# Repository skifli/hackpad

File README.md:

# hackpad

- [hackpad](#hackpad)
  - [Project Structure](#project-structure)
  - [Journal](#journal)
  - [PCB](#pcb)
    - [Schematic](#schematic)
    - [PCB Design](#pcb-design)
    - [PCB Render](#pcb-render)
  - [CAD](#cad)
  - [BOM](#bom)
  - [Software](#software)

| Cover                            | Exploded View                                    |
| -------------------------------- | ------------------------------------------------ |
|  |  |

> [!IMPORTANT]\
> Since submission, the BOM price has decreased to $119.89 from above $150 (check [#bom](#bom) for more information).

A fully wireless macropad with 14 Choc v1 Ambient Nocturnal switches, 2 rotary encoders (with a push-button each), and a small screen! The case is in two sections - a top and bottom, and joins together via 8 magnets, half in each side of the case (you can see the magnet holes in the various views).

I made this project because when programming / doing CAD design there are so many different shortcuts I use to make sketches, change orbit types, etc, and these require a lot of clicks. These all could be streamlined a lot more with the use of a macropad - which is why I made this one. I decided to also add a screen so I could easily see which profile I'm on and switch (likely by rotating a rotary encoder while it is held down), and the two rotary encoders to easily control multiple audio streams (mainly YouTube vs. Spotify).

## Project Structure

> [!IMPORTANT]\
> Only includes files / folders relevant to admin that would benefit from explanation.

```
└── 📁hackpad
    └── 📁design
        └── 📁cad
            ├── case_bottom.step
            ├── case_top.step
        └── 📁pcb
            ├── ... # Contains the KiCad directory for the PCB
        └── 📁plate
            ├── ... # Contains the KiCad directory for the plate, which is made from an exported DXF from the Fusion 360 Sketch (plate.dxf)
    ├── JOURNAL.md # The journal of the design process
    └── README.md # This file
```

> [!WARNING]\
> The KiCad plate PCB gives [malformed outline warnings](JOURNAL.md#20072025) and doesn't show correctly in 3D view - no idea why, but when exported with the Fabrication Toolkit and imported into JLCPCB it's totally fine 🗿 (if it works, it works™). 

## Journal

The [journal](JOURNAL.md) contains each day's work, logged, with the aid of images. Total time is at the top and each day has its time logged. There is also a Table of Contents for easy navigation :).

> [!NOTE]\
> Total time spent: **60h**

## PCB

### Schematic

### PCB Design

### PCB Render

## CAD

| Case Top Side View (from the bottom)                 | Case Bottom Side View (from the top)                       |
| ---------------------------------------------------- | ---------------------------------------------------------- |
|  |  |

| Case Plate                                     | Case USB Port                              |
| ---------------------------------------------- | ------------------------------------------ |
|  |  |

## BOM

> [!TIP]\
> The BOM is split into the different companies from which the components would be bought, with an empty line delimiting them. As well as this, at the end of each section, the total price for that provider, along with the shipping, is provided in the **Price** column. There is also the total price in the aforementioned column on the last row.

> [!NOTE]\
> I found the promo code **KBDNEWS** for Mechboards (a UK-based merchant) 5% off so I included that in the BOM as well to explain the decrease in total price.

<details closed>
<summary>BOM in table format</summary>

| Component                               | Description                     | Notes                                            | Qty | Price      | Shipping   | Provider   | Link                                                                                                               |
| --------------------------------------- | ------------------------------- | ------------------------------------------------ | --- | ---------- | ---------- | ---------- | ------------------------------------------------------------------------------------------------------------------ |
| Kailh Choc Hotswap Sockets              | V1 (Pack of 10)                 |                                                  | 2   | £6.00      | £1.81      | Mechboards | [Link](https://mechboards.co.uk/products/kailh-choc-hotswap-sockets?variant=40427263754445)                        |
| DDC Choc (v1) PBT Blank Keycaps - White | White Keycaps / 1u (Pack of 10) |                                                  | 1   | £4.50      | –          | Mechboards | [Link](https://mechboards.co.uk/products/ddc-choc-pbt-blank-keycaps?variant=47587896426701)                        |
| DDC Choc (v1) PBT Blank Keycaps - Black | Black Keycaps / 1u (Pack of 10) |                                                  | 1   | £4.50      | –          | Mechboards | [Link](https://mechboards.co.uk/products/ddc-choc-pbt-blank-keycaps?variant=47405364576461)                        |
| lowprokb Choc (V1) Ambients Nocturnal   | (Pack of 10)                    |                                                  | 2   | £19.00     | –          | Mechboards | [Link](https://mechboards.co.uk/products/lowprokb-ambients-silent-linear-nocturnal-choc-v1?variant=47588169908429) |
| KBDNEWS Promo Code                      |                                 |                                                  | –   | –£0.94     | –          | –          | –                                                                                                                  |
| **Total (Mechboards)**                  |                                 |                                                  |     | **£34.11** | *Included* |            |                                                                                                                    |
| nice!nano v2                            |                                 | Compatible board                                 | 1   | £2.99      | £2.99      | AliExpress | [Link](https://www.aliexpress.com/item/1005006035267231.html)                                                      |
| nice!view                               |                                 | Compatible screen (without headers)              | 1   | £12.69     | –          | AliExpress | [Link](https://www.aliexpress.com/item/1005008115497843.html)                                                      |
| Header Pins                             | 1x5 Pins (50 PCS)               | Headers for the above screen                     | 1   | £1.15      | –          | AliExpress | [Link](https://www.aliexpress.com/item/4000988113226.html)                                                         |
| Tiny Disc Magnet                        | 4x3mm (100 PCS)                 | To join the top and bottom of the case           | 1   | £4.86      | £2.96      | AliExpress | [Link](https://www.aliexpress.com/item/1005009177139622.html)                                                      |
| SMT SOD-123 Diodes                      | 100 PCS                         | For the switches                                 | 1   | £1.11      | –          | AliExpress | [Link](https://www.aliexpress.com/item/4000685043735.html)                                                         |
| Heat Shrink Tubes                       |                                 | For wiring between switch, battery, nice!nano v2 | 1   | £1.35      | –          | AliExpress | [Link](https://www.aliexpress.com/item/1005008146302901.html)                                                      |
| JST PH Plug Connector with Wire (M)     | MALE 2P 100mm (5 PCS)           | For battery wiring                               | 1   | £0.34      | £1.94      | AliExpress | [Link](https://www.aliexpress.com/item/1005008864177105.html)                                                      |
| JST PH Plug Connector with Wire (F)     | FEMALE 2P 100mm (5 PCS)         | For battery wiring                               | 1   | £0.49      | £1.94      | AliExpress | [Link](https://www.aliexpress.com/item/1005008864177105.html)                                                      |
| Bumper Feet                             | 5mm x 2mm (100 PCS)             | For bottom of the case and PCB                   | 1   | £1.59      | –          | AliExpress | [Link](https://www.aliexpress.com/item/1005004068119765.html)                                                      |
| Toggle Switch                           | K031b004-G3                     | To power on/off the system                       | 1   | £1.94      | –          | AliExpress | [Link](https://www.aliexpress.com/item/1005009306874094.html)                                                      |
| 3.7V 150mAh                             | 1 battery                       | To power the system                              | 1   | £4.74      | N/A        | AliExpress | [Link](https://www.aliexpress.com/item/1005004084377638.html)                                                      |
| Rotary Encoder w/ Push Button           | 5 PCS                           |                                                  | 1   | £1.08      | –          | AliExpress | [Link](https://www.aliexpress.com/item/1005005983134515.html)                                                      |
| **Total (AliExpress)**                  |                                 |                                                  |     | **£42.35** | *Included* |            |                                                                                                                    |
| Plate & PCB                             |                                 |                                                  |     | £5.94      | £6.11      | JLCPCB     | N/A                                                                                                                |
| **Total (JLCPCB)**                      |                                 |                                                  |     | **£12.05** | *Included* |            |                                                                                                                    |
| **TOTAL**                               |                                 |                                                  |     | **£88.51** | *Included* |            |                                                                                                                    |  |

</details>

> [!IMPORTANT]\
> Please disregard a lot of what is in the below text. After someone in the Slack (@Toby), introduced me to the world of AliExpress, I completely redid the BOM. It is now $119.89 (yes that is USD lol), so way under the limit. Thanks a lot dude :).

The BOM can be found in [`/bom.csv`](bom.csv). Since this is my first ever hardware project, I decided to go for some products that were easier to find footprints / symbols in KiCad for. With hindsight, spending the amount of money I now have to on a nice! nano v2 or nice!view (which I landed on because I chose the nice! nano v2) isn't really necessary. So, in future projects I'll choose other, cheaper components - but for this one I've already designed the PCB etc, and was very new to this whole world of design, and so decided to go with components that I was more confident with.

The Seeed Studio XIAO RP2040 didn't have enough GPIO anyway since I needed a 4x4 key matrix (so 8 pins), 4 other GPIO for the 2 rotary encoders, and the screen pins. Now, unfortunately this does mean the price is way over $150. This is in part because I also forgot Hackclub operates in USD and so was sure I would be in price range until 2 days ago, at which point I had a heart attack 😭. I'll try to cover the rest myself... not really sure how that'll go because I need to buy solder and other stuff since this is my first hardware project (which is already a lot of money), but we'll see... I'm not sure if Hackclub has a thing with JLCPCB for cheaper PCBs but if so that would reduce the total cost, although it might still be just over $150.

## Software

Will be _mostly_ added once the physical components are received and assembled, as I don't want to start writing code and then find out it doesn't work because I accidentally used libraries for different components, or something similar to that.

I have added some stuff in the [`/software`](software) directory though.

---
<sub>Thanks to [Hackclub](https://hackclub.com) for such an amazing opportunity - this project was made by [@skifli](https://github.com/skifli) with 🩷, under the [MIT License](LICENSE).</sub>

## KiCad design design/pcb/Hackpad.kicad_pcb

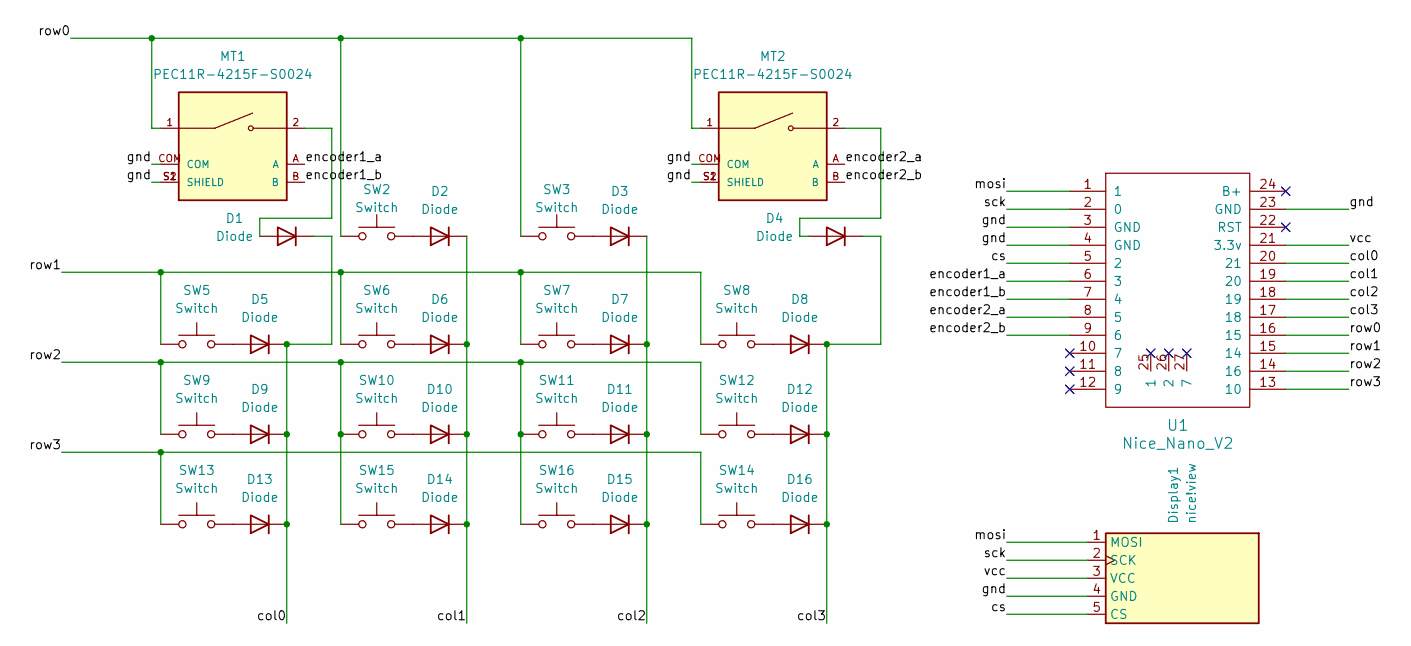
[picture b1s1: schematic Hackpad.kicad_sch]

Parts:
D1, D2, D3, D4, D5, D6, D7, D8, D9, D10, D11, D12, D13, D14, D15, D16: Diode; D_SOD-123; PARTREV 5
Display1: nice!view; nice_view
MT1, MT2: PEC11R-4215F-S0024; XDCR_PEC11R-4215F-S0024; PARTREV Rev. 09/19
SW2, SW3, SW5, SW6, SW7, SW8, SW9, SW10, SW11, SW12, SW13, SW14, SW15, SW16: Switch; Hotswap_Choc_V1_1.00u
U1: Nice_Nano_V2

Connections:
/col0: D1.1 (K), D5.1 (K), D9.1 (K), D13.1 (K), U1.20 (21)
/col1: D2.1 (K), D6.1 (K), D10.1 (K), D14.1 (K), U1.19 (20)
/col2: D3.1 (K), D7.1 (K), D11.1 (K), D15.1 (K), U1.18 (19)
/col3: D4.1 (K), D8.1 (K), D12.1 (K), D16.1 (K), U1.17 (18)
/cs: Display1.5 (CS), U1.5 (2)
/encoder1_a: MT1.A, U1.6 (3)
/encoder1_b: MT1.B, U1.7 (4)
/encoder2_a: MT2.A, U1.8 (5)
/encoder2_b: MT2.B, U1.9 (6)
/gnd: Display1.4 (GND), MT1.COM, MT1.S1 (SHIELD), MT1.S2 (SHIELD), MT2.COM, MT2.S1 (SHIELD), MT2.S2 (SHIELD), U1.3 (GND), U1.4 (GND), U1.23 (GND)
/mosi: Display1.1 (MOSI), U1.1
/row0: MT1.1, MT2.1, SW2.1, SW3.1, U1.16 (15)
/row1: SW5.1, SW6.1, SW7.1, SW8.1, U1.15 (14)
/row2: SW9.1, SW10.1, SW11.1, SW12.1, SW15.1, SW16.1, U1.14 (16)
/row3: SW13.1, SW14.1, U1.13 (10)
/sck: Display1.2 (SCK), U1.2 (0)
/vcc: Display1.3 (VCC), U1.21 (3.3v)
unnamed: D1.2 (A), MT1.2
unnamed: D2.2 (A), SW2.2
unnamed: D3.2 (A), SW3.2
unnamed: D4.2 (A), MT2.2
unnamed: D5.2 (A), SW5.2
unnamed: D6.2 (A), SW6.2
unnamed: D7.2 (A), SW7.2
unnamed: D8.2 (A), SW8.2
unnamed: D9.2 (A), SW9.2
unnamed: D10.2 (A), SW10.2
unnamed: D11.2 (A), SW11.2
unnamed: D12.2 (A), SW12.2
unnamed: D13.2 (A), SW13.2
unnamed: D14.2 (A), SW15.2
unnamed: D15.2 (A), SW16.2
unnamed: D16.2 (A), SW14.2

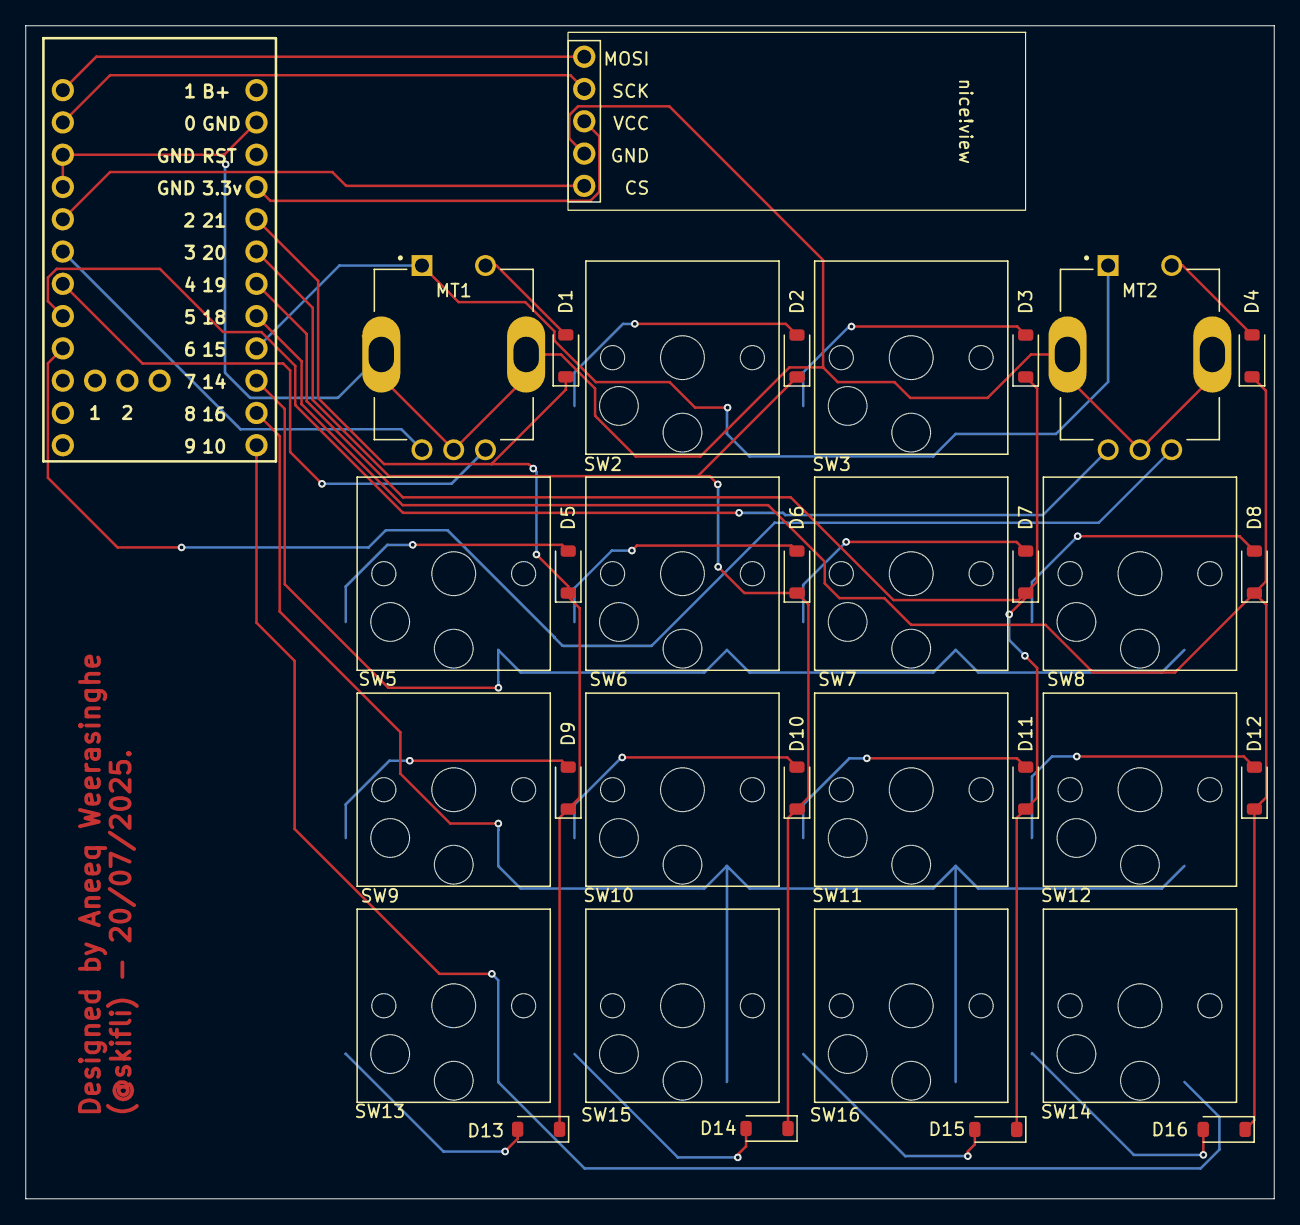
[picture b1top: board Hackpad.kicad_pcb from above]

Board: 2 copper layers, 98.2 x 92.3 mm, 34 parts (0 on the bottom side), 33 nets.

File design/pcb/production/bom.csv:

Designator,Footprint,Quantity,Value,LCSC Part #
"D1, D10, D11, D12, D13, D14, D15, D16, D2, D3, D4, D5, D6, D7, D8, D9",D_SOD-123,16,Diode,
DISPLAY1,nice_view,1,nice!view,
"MT1, MT2",XDCR_PEC11R-4215F-S0024,2,PEC11R-4215F-S0024,
"SW10, SW11, SW12, SW13, SW14, SW15, SW16, SW2, SW3, SW5, SW6, SW7, SW8, SW9",Hotswap_Choc_V1_1.00u,14,Switch,
U1,Nice_Nano_V2,1,Nice_Nano_V2,

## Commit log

2025-06-27 feat: init `JOURNAL.md`
2025-06-30 feat: add <30/06/2025 to `JOURNAL.md`
2025-06-30 fix: heading order in `JOURNAL.md`
2025-07-03 feat: added upto 02/07/2025
2025-07-03 fix: links not updated
2025-07-19 feat: add cover and finish journal
2025-07-19 feat: try macropad
2025-07-19 feat: update dimensions of covers
2025-07-20 feat: update views
2025-07-20 feat: add pcb images
2025-07-20 feat: add case views + BOM
2025-07-20 fix: csv format?
2025-07-20 feat: add bom, update `README.md`
2025-07-20 fix: forgot to update total in `bom.csv`
2025-07-20 feat: update BOM in `README.md`
2025-07-20 feat: reorganise journal images
2025-07-21 feat: update `README.md`
2025-07-21 fix: journal link in `README.md`
2025-07-21 feat: add bom in `README.md`
2025-07-21 fix: details default closed
2025-07-21 feat: update `bom.csv` to be way cheaper
2025-07-21 feat: add section about BOM price decrease
2025-07-21 fix: bom in `README.md`
2025-07-21 fix: tables in `README.md` BOM
2025-07-21 fix: lack of GBP sign
2025-07-21 fix: add jlcpcb pricing
2025-07-21 fix: case for 5mm bumper feet
2025-07-21 fix: add jlcpcb price to `README.md` BOM
2025-07-22 feat: add zmk stuff
2025-07-24 feat: reduce BOM price even more!!!
